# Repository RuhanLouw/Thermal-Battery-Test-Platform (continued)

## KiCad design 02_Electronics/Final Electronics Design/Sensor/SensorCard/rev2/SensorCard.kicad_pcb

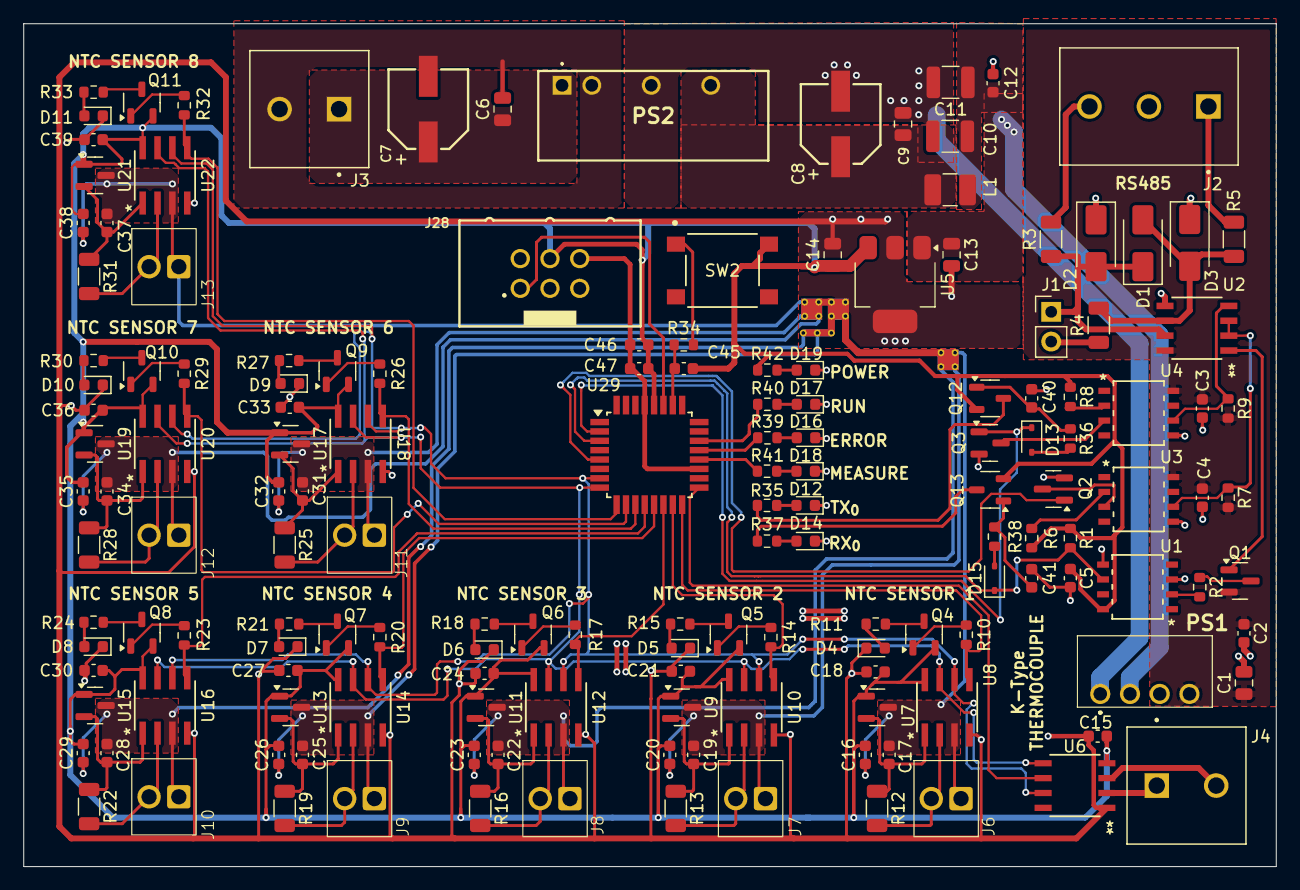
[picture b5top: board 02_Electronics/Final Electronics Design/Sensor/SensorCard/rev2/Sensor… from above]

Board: 2 copper layers, 107.0 x 72.0 mm, 162 parts (0 on the bottom side), 107 nets.

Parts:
C1, C6, C8, C13, C14: 10uF; C_0805_2012Metric
C2: 1uF; C_0603_1608Metric
C3, C4, C5, C12, C15, C17, C18, C19, C21, C22, C24, C25, C27, C28, C30, C31, C33, C34, C36, C37, C39, C40, C41, C45: 0.1uF; C_0603_1608Metric
C7: 47uF; WCAP-ASLI_6.3X5.5_DXL_47uF
C9: 100uF; WCAP-ASLI_6.3X7.7_DXL_
C10, C11: 22uF; C_1210_3225Metric
C16, C20, C23, C26, C29, C32, C35, C38: 2.2uF; C_0603_1608Metric
C46: 1u; C_0603_1608Metric
C47: 10n; C_0603_1608Metric
D1, D2, D3: SMAJ5.0CA; D_SMA
D4, D5, D6, D7, D8, D9, D10, D11, D12, D14, D16, D17, D18, D19: LED; LED_0603_1608Metric
D13, D15: SD101CWS-TP; D_SOD-323
J1: Conn_01x02; PinHeader_1x02_P2.54mm_Vertical
J2: RS485; TE_282857-3_screw
J3, J4: Screw_Terminal_01x02; TE_282857-2_screw
J6, J7, J8, J9, J10, J11, J12, J13: Screw_Terminal_01x02; TERM BLOCK 2P HORIZON 2.54MM PCB
J28: Conn_02x03_Top_Bottom; 61200621621
L1: 4.7uH; L_1210_3225Metric_Pad1.42x2.65mm_HandSolder_cad
NT4: NetTie_3; NetTie-3_THT_Pad0.3mm
NT5, NT6, NT7: NetTie_4; NetTie-4_THT_Pad0.3mm
PS1: NME0505SC
PS2: NMG1205SC
Q1, Q2, Q3: BSS84; SOT-23
Q4, Q5, Q6, Q7, Q8, Q9, Q10, Q11: PNP; SOT-23-3 MMBT3906
Q12, Q13: MMBT2907A-TP; SOT-23-3 MMBT2907A
R1, R7, R9: 1k; R_0603_1608Metric
R2, R6, R8: 120; R_0603_1608Metric
R3, R4, R5: 120; R_1206_3216Metric
R10, R14, R17, R20, R23, R26, R29, R32, R36, R38: 10k; R_0603_1608Metric
R11, R15, R18, R21, R24, R27, R30, R33, R35, R37, R39, R40, R41, R42: 300; R_0603_1608Metric
R12, R13, R16, R19, R22, R25, R28, R31: 10k; R_1206_3216Metric
R34: 330; R_0603_1608Metric
SW2: SW_Push; SWITCH_43SMTR92LFS
U1, U3, U4: HCPL-0501-500E; SO8_HCPL-0501-500_BRA
U2: SP485ECN-L; NSOIC-8
U5: MIC5239-3.3YS; SOT-223-3_TabPin2
U6: MAX31855KASA+T; 21-0041B_8_MXM
U7, U9, U11, U13, U15, U17, U19, U21: REF3330AIDBZR; SOT-23
U8, U10, U12, U14, U16, U18, U20, U22: MCP3201; SOIC8-N_MC_MCH
U29: AVR128DA32x-xPT; TQFP-32_7x7mm_P0.8mm

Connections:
3.3V_{DD}: C5.2, C14.1, C15.2, C16.2, C18.2, C20.2, C21.2, C23.2, C24.2, C26.2, C27.2, C29.2, C30.2, C32.2, C33.2, C35.2, C36.2, C38.2, C39.2, C45.1, C46.1, C47.1, J28.4, Q4.3 (E), Q5.3 (E), Q6.3 (E), Q7.3 (E), Q8.3 (E), Q9.3 (E), Q10.3 (E), Q11.3 (E), Q12.1 (E), Q13.1 (E), R1.2, R6.1, R8.1, R42.1, SW2.2, U1.8 (V_{CC}), U5.3 (VO), U6.4 (VCC), U7.1 (IN), U8.8 (Vdd), U9.1 (IN), U10.8 (Vdd), U11.1 (IN), U12.8 (Vdd), U13.1 (IN), U14.8 (Vdd), U15.1 (IN), U16.8 (Vdd), U17.1 (IN), U18.8 (Vdd), U19.1 (IN), U20.8 (Vdd), U21.1 (IN), U22.8 (Vdd), U29.28 (VDD)
5V_{DD_unfiltered}: C8.1, C9.1, L1.2, PS2.6 (+VOUT)
5V_{DD}: C10.1, C11.1, C12.1, C13.1, L1.1, PS1.4 (+VIN), U5.1 (VI)
5V_{RS485}: C1.1, C2.1, C3.1, C4.1, PS1.7 (+VOUT), Q1.2 (S), R7.2, R9.2, U2.8 (VCC), U3.8 (V_{CC}), U4.8 (V_{CC})
12V_{CC}: C6.1, C7.1, J3.1, PS2.1 (_+VIN)
ERROR: R39.1, U29.21 (XTAL32K2/PF1)
GNDA_{NTC1}: C16.1, C17.1, J6.2, NT6.2, U7.3 (GND), U8.3 (IN-)
GNDA_{NTC2}: C19.1, C20.1, J7.2, NT6.4, U9.3 (GND), U10.3 (IN-)
GNDA_{NTC3}: C22.1, C23.1, J8.2, NT6.3, U11.3 (GND), U12.3 (IN-)
GNDA_{NTC4}: C25.1, C26.1, J9.2, NT4.2, U13.3 (GND), U14.3 (IN-)
GNDA_{NTC5}: C28.1, C29.1, J10.2, NT4.3, U15.3 (GND), U16.3 (IN-)
GNDA_{NTC6}: C31.1, C32.1, J11.2, NT5.4, U17.3 (GND), U18.3 (IN-)
GNDA_{NTC7}: C34.1, C35.1, J12.2, NT5.2, U19.3 (GND), U20.3 (IN-)
GNDA_{NTC8}: C37.1, C38.1, J13.2, NT5.3, U21.3 (GND), U22.3 (IN-)
GND_{CC}: C6.2, C7.2, J3.2, PS2.2 (-VIN)
GND_{DD}: C5.1, C8.2, C9.2, C10.2, C11.2, C12.2, C13.2, C14.2, C15.1, C18.1, C21.1, C24.1, C27.1, C30.1, C33.1, C36.1, C39.1, C40.1, C41.1, C46.2, C47.2, D4.1 (K), D5.1 (K), D6.1 (K), D7.1 (K), D8.1 (K), D9.1 (K), D10.1 (K), D11.1 (K), D12.1 (K), D14.1 (K), D16.1 (K), D17.1 (K), D18.1 (K), D19.1 (K), J28.6, NT7.1, PS1.1 (-VIN), PS2.4 (-VOUT), Q2.2 (S), Q3.2 (S), U1.5 (GND), U5.2 (GND), U6.1 (GND), U8.4 (Vss), U10.4 (Vss), U12.4 (Vss), U14.4 (Vss), U16.4 (Vss), U18.4 (Vss), U20.4 (Vss), U22.4 (Vss), U29.19 (GND), U29.29 (GND)
GND_{RS485}: C1.2, C2.2, C3.2, C4.2, D1.1 (A1), D3.1 (A1), J2.2, PS1.5 (-VOUT), U1.3 (CAT), U2.5 (GND), U3.5 (GND), U4.5 (GND)
MCU_RESET: C45.2, R34.1, U29.26 (~RESET/PF6)
MCU_UDPI: J28.1, U29.27 (UPDI)
MEAS: R41.1, U29.20 (XTAL32K1/PF0)
NTC1_~CS: R10.1, U8.5 (~CS/SHDN), U29.16 (PD6)
NTC2_~CS: R14.1, U10.5 (~CS/SHDN), U29.15 (PD5)
NTC3_~CS: R17.1, U12.5 (~CS/SHDN), U29.14 (PD4)
NTC4_~CS: R20.1, U14.5 (~CS/SHDN), U29.13 (PD3)
NTC5_~CS: R23.1, U16.5 (~CS/SHDN), U29.12 (PD2)
NTC6_~CS: R26.1, U18.5 (~CS/SHDN), U29.11 (PD1)
NTC7_~CS: R29.1, U20.5 (~CS/SHDN), U29.10 (PD0)
NTC8_~CS: R32.1, U22.5 (~CS/SHDN), U29.9 (PC3)
unnamed: D1.2 (A2), D2.1 (A1), J1.1, R3.1, U2.7 (B)
unnamed: D2.2 (A2), D3.2 (A2), R4.2, R5.1, U2.6 (A)
unnamed: D4.2 (A), R11.1
unnamed: D5.2 (A), R15.1
unnamed: D6.2 (A), R18.1
unnamed: D7.2 (A), R21.1
unnamed: D8.2 (A), R24.1
unnamed: D9.2 (A), R27.1
unnamed: D10.2 (A), R30.1
unnamed: D11.2 (A), R33.1
unnamed: D12.2 (A), R35.2
unnamed: D13.2 (A), R36.1
unnamed: D14.2 (A), R37.2
unnamed: D15.2 (A), R38.1
unnamed: D16.2 (A), R39.2
unnamed: D17.2 (A), R40.2
unnamed: D18.2 (A), R41.2
unnamed: D19.2 (A), R42.2
unnamed: J1.2, R4.1
unnamed: J2.1, R5.2
unnamed: J2.3, R3.2
unnamed: J4.1, U6.2 (T-)
unnamed: J4.2, U6.3 (T+)
unnamed: J6.1, R12.2, U8.2 (IN+)
unnamed: J7.1, R13.2, U10.2 (IN+)
unnamed: J8.1, R16.2, U12.2 (IN+)
unnamed: J9.1, R19.2, U14.2 (IN+)
unnamed: J10.1, R22.2, U16.2 (IN+)
unnamed: J11.1, R25.2, U18.2 (IN+)
unnamed: J12.1, R28.2, U20.2 (IN+)
unnamed: J13.1, R31.2, U22.2 (IN+)
unnamed: NT4.1, NT7.4
unnamed: NT5.1, NT7.3
unnamed: NT6.1, NT7.2
unnamed: Q1.3 (D), R2.1
unnamed: Q1.1 (G), U2.1 (RO)
unnamed: Q2.3 (D), U3.3 (CAT)
unnamed: Q3.3 (D), U4.3 (CAT)
unnamed: Q4.2 (B), R10.2
unnamed: Q4.1 (C), R11.2
unnamed: Q5.2 (B), R14.2
unnamed: Q5.1 (C), R15.2
unnamed: Q6.2 (B), R17.2
unnamed: Q6.1 (C), R18.2
unnamed: Q7.2 (B), R20.2
unnamed: Q7.1 (C), R21.2
unnamed: Q8.2 (B), R23.2
unnamed: Q8.1 (C), R24.2
unnamed: Q9.2 (B), R26.2
unnamed: Q9.1 (C), R27.2
unnamed: Q10.2 (B), R29.2
unnamed: Q10.1 (C), R30.2
unnamed: Q11.2 (B), R32.2
unnamed: Q11.1 (C), R33.2
unnamed: C40.2, Q12.2 (B), R36.2
unnamed: Q12.3 (C), R35.1
unnamed: C41.2, Q13.2 (B), R38.2
unnamed: Q13.3 (C), R37.1
unnamed: R34.2, SW2.1
unnamed: R2.2, U1.2 (AN)
unnamed: R7.1, U2.2 (~RE), U2.3 (DE), U3.6 (V_{OUT})
unnamed: R9.1, U2.4 (DI), U4.6 (V_{OUT})
unnamed: R6.2, U3.2 (AN)
unnamed: R8.2, U4.2 (AN)
unnamed: C17.2, R12.1, U7.2 (OUT), U8.1 (Vref)
unnamed: C19.2, R13.1, U9.2 (OUT), U10.1 (Vref)
unnamed: C22.2, R16.1, U11.2 (OUT), U12.1 (Vref)
unnamed: C25.2, R19.1, U13.2 (OUT), U14.1 (Vref)
unnamed: C28.2, R22.1, U15.2 (OUT), U16.1 (Vref)
unnamed: C31.2, R25.1, U17.2 (OUT), U18.1 (Vref)
unnamed: C34.2, R28.1, U19.2 (OUT), U20.1 (Vref)
unnamed: C37.2, R31.1, U21.2 (OUT), U22.1 (Vref)
RUN: R40.1, U29.22 (PF2)
RX_{RS485}: D15.1 (K), R1.1, U1.6 (V_{OUT}), U29.3 (PA5)
SPI0_MISO: U6.7 (SO), U8.6 (Dout), U10.6 (Dout), U12.6 (Dout), U14.6 (Dout), U16.6 (Dout), U18.6 (Dout), U20.6 (Dout), U22.6 (Dout), U29.7 (PC1)
SPI0_SCK: U6.5 (SCK), U8.7 (CLK), U10.7 (CLK), U12.7 (CLK), U14.7 (CLK), U16.7 (CLK), U18.7 (CLK), U20.7 (CLK), U22.7 (CLK), U29.8 (PC2)
TX_{RS485_EN}: Q2.1 (G), U29.5 (PA7)
TX_{RS485}: D13.1 (K), Q3.1 (G), U29.2 (PA4)
Therm_~CS: U6.6 (*CS), U29.17 (VREFA/PD7)

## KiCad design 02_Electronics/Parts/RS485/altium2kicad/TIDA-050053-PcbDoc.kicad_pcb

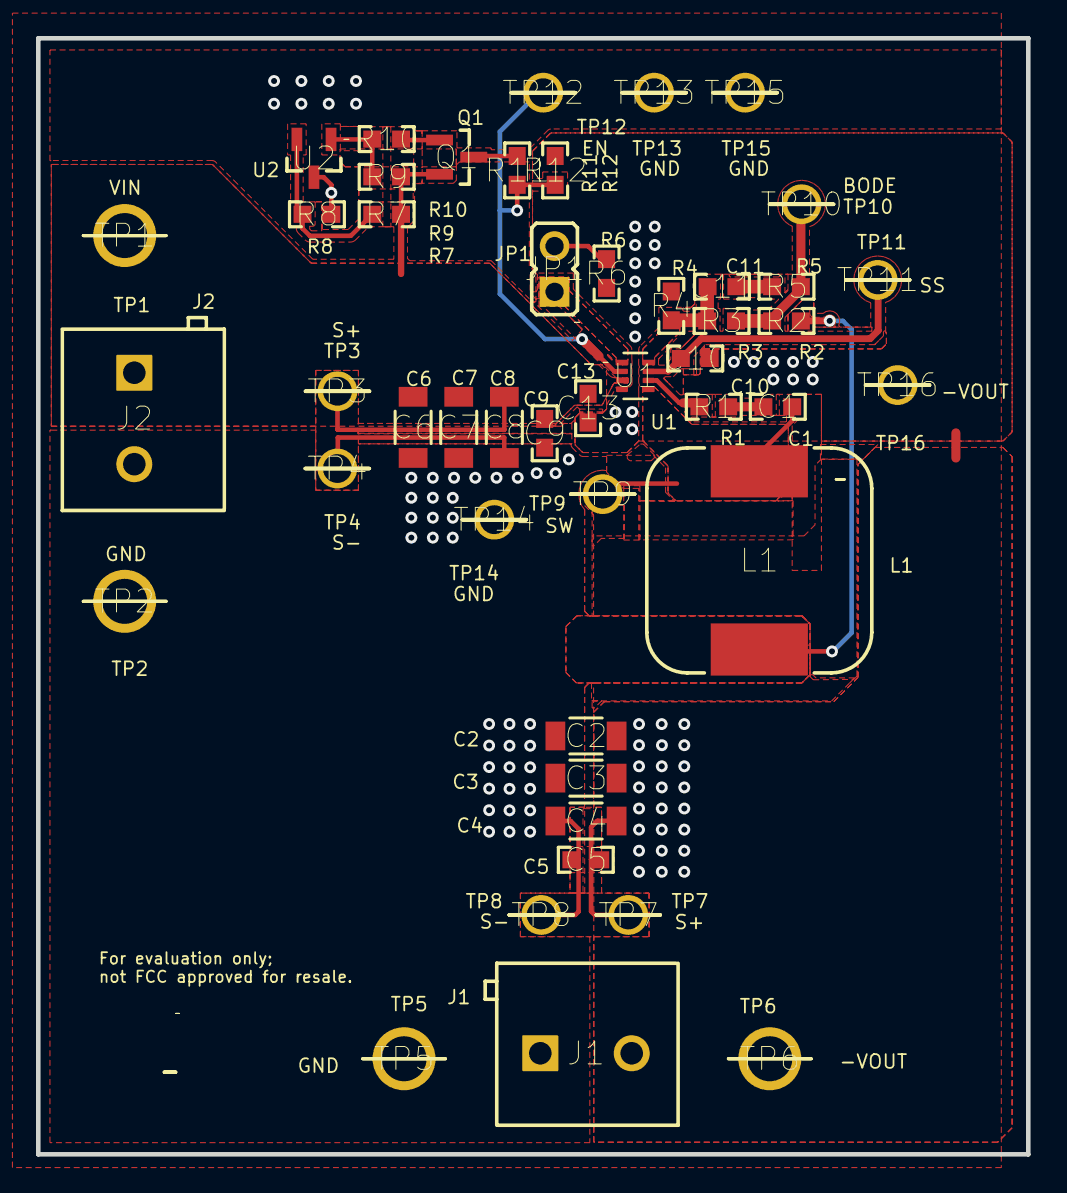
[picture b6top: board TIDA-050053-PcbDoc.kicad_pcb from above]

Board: 2 copper layers, 55.0 x 62.0 mm, 47 parts (0 on the bottom side), 17 nets.

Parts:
C1: C1; 0603
C2: C2; 1206_180
C3: C3; 1206_180
C4: C4; 1206_180
C5: C5; 0603
C6: C6; 1206_190
C7: C7; 1206_190
C8: C8; 1206_190
C9: C9; 0603
C10: C10; 0603
C11: C11; 0603
C13: C13; 0603
J1: J1; On-Shore_ED120_2DS
J2: J2; On-Shore_ED120_2DS
JP1: JP1; Sullins_PBC02SAAN
L1: L1; WE-PD_1280
Q1: Q1; SOT-23
R1: R1; 0603
R2: R2; 0603
R3: R3; 0603
R4: R4; 0603
R5: R5; 0603
R6: R6; 0603
R7: R7; 0603
R8: R8; 0603
R9: R9; 0603
R10: R10; 0603
R11: R11; 0603
R12: R12; 0603
TP1: TP1; Keystone1502-2
TP2: TP2; Keystone1502-2
TP3: TP3; Keystone5010
TP4: TP4; Keystone5011
TP5: TP5; Keystone1502-2
TP6: TP6; Keystone1502-2
TP7: TP7; Keystone5010
TP8: TP8; Keystone5011
TP9: TP9; Keystone5014
TP10: TP10; Keystone5014
TP11: TP11; Keystone5014
TP12: TP12; Keystone5014
TP13: TP13; Keystone5011
TP14: TP14; Keystone5011
TP15: TP15; Keystone5011
TP16: TP16; Keystone5010
U1: U1; DRL0008A-MFG
U2: U2; MF03A_N

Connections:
-Vo: C2.2, C3.2, C4.2, C5.2, C10.2, C13.2, J1.2, R4.1, R6.1, R12.1, TP6.1, TP7.1, TP16.1, U1.4
BST: R1.1, U1.6
EN: R11.2, R12.2, TP12.1, U1.2
FB: C11.2, R3.1, R4.2, U1.8
GND: C2.1, C3.1, C4.1, C5.1, C6.2, C7.2, C8.2, C9.2, J1.1, J2.2, L1.2, R2.2, R8.1, TP2.1, TP4.1, TP5.1, TP8.1, TP13.1, TP14.1, TP15.1, U2.3
NetC1_2: C1.2, R1.2
NetC11_1: C11.1, R5.1
NetJP1_2: JP1.2, R6.2
NetQ1_1: Q1.1, R10.2
NetQ1_3: Q1.3, R11.1
NetR2_1: R2.1, R3.2, R5.2, TP10.1
NetR7_1: R7.1, R8.2, U2.2
NetR9_1: R9.1, R10.1, U2.1
RT: JP1.1, U1.1
SS: C10.1, TP11.1, U1.7
SW: C1.1, L1.1, TP9.1, U1.5
VIN: C6.1, C7.1, C8.1, C9.1, C13.1, J2.1, Q1.2, R7.2, R9.2, TP1.1, TP3.1, U1.3
